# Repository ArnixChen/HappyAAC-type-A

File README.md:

# HappyAAC-type-A
## An open-source main-board to make AAC device makers Happy ;)

## HappyAAC type A
#### 尺寸 8cm x 5cm 角落圓孔直徑 2.86mm
#### 它是一塊針對AAC溝通需求設計的開放電路板,使用者只要把必要的元件焊上電路板,就可以開始動手實作各種功能,免去手工連接大量線路的困難。

1. 使用 Sparkfun Pro Micro控制板, 支援鍵盤或滑鼠模擬功能
2. 內建 BB-4056 鋰電池充電模組線路,有插座可接鋰池及充電
3. 內建 DFPlayer Mini MP3 模組線路,內含一組音訊Line Out 用的插座,可接擴音喇叭,另有一組最大3W迷喇叭接插座
4. 一組音量旋鈕插座
5. 支援最多24個按鈕或特殊開關接點(沒有與其他功能衝突時)
6. 兩組獨立I2C裝置接點
7. 紅外線接收接座, 可以接遙控訊號
8. 紅外線發射接座,可以遙控其他的裝置
9. 留有16組GPIO +VCC+GND 接點,滿足特殊用途的需求
10. 它使用KiCad (open source)電路軟體設計, 並提供原始檔, 可以自己修改設計。

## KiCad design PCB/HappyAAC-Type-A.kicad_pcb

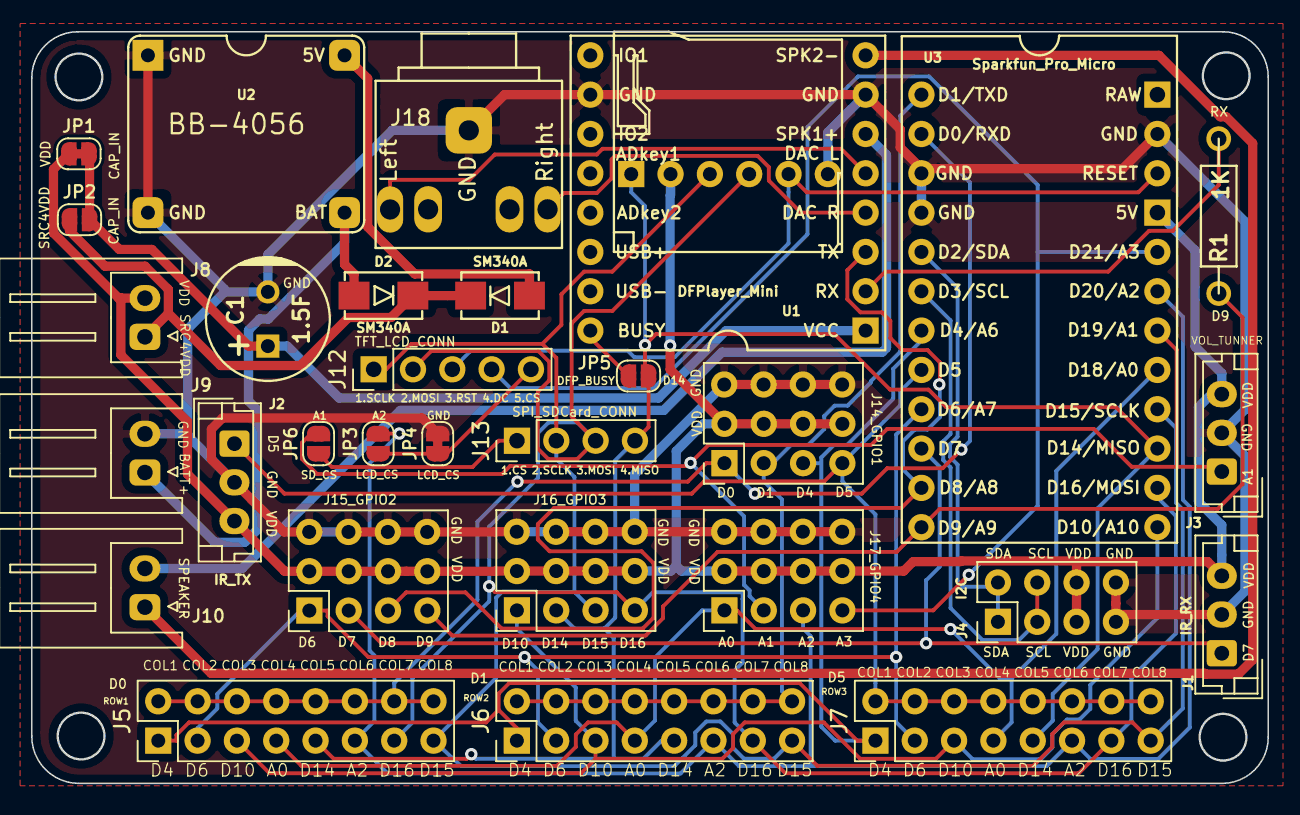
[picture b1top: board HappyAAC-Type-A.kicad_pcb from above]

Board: 2 copper layers, 79.8 x 48.5 mm, 31 parts (0 on the bottom side), 33 nets.

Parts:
C1: 1.5F; CAP_pol_DIP_D8mm
D1, D2: SM340A; SMA_DO214AC_M_SM340A
J1: IR_RX; JST_EH_B3B-EH-A_1x03_P2.50mm_Vertical
J2: IR_TX; JST_EH_B3B-EH-A_1x03_P2.50mm_Vertical
J3: VOL_TUNNER; JST_EH_B3B-EH-A_1x03_P2.50mm_Vertical
J4: I2C; PinHeader_2x04_P2.54mm_Vertical_PadHole0.9mm
J5: ROW1; PinHeader_2x08_P2.54mm_Vertical
J6: ROW2; PinHeader_2x08_P2.54mm_Vertical
J7: ROW3; PinHeader_2x08_P2.54mm_Vertical
J8: PWR_SW; PEC-2503-2H.JST_XH_S2B-XH-A_1x02_P2.50mm_Horizontal
J9: Batt; PEC-2503-2H.JST_XH_S2B-XH-A_1x02_P2.50mm_Horizontal
J10: SPEAKER; PEC-2503-2H.JST_XH_S2B-XH-A_1x02_P2.50mm_Horizontal
J11: ICSP; ICSP_PinHeader_1x06_P2.54mm_Horizontal
J12: TFT_LCD; PinHeader_1x05_P2.54mm_Vertical
J13: SDCard_Conn; PinHeader_1x04_P2.54mm_Vertical
J14_GPIO1, J15_GPIO2, J16_GPIO3, J17_GPIO4: Conn_03x04_Odd_Even_VSG; PinHeader_3x04_P2.54mm_Vertical_PadHole0.9mm
J18: AudioJack; Jack_3.5mm_Arnix_5pin_AudioJack4_Ground_Horizontal
JP1, JP4: SolderJumper_2_Bridged; SolderJumper-2_P1.3mm_Bridged_RoundedPad1.0x1.5mm
JP2, JP3, JP5, JP6: SolderJumper_2_Open; SolderJumper-2_P1.3mm_Open_RoundedPad1.0x1.5mm
R1: 1K; RES_DIP_0.25W_10mm
U1: DFPlayer_Mini; DFPlayer_Mini_BigPad
U2: BB-4056
U3: Sparkfun_Pro_Micro; Sparkfun_Pro_Micro_BigPad

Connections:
+5V: D1.2, U2.4
+BATT: D2.2, J9.1, U2.3
/A0: J5.7, J6.7, J7.7, J17_GPIO4.1, U3.17
/A1: J3.1, J17_GPIO4.2, JP6.2, U3.18
/A2: J5.11, J6.11, J7.11, J17_GPIO4.3, JP3.2, U3.19
/A3: J12.4, J17_GPIO4.4, U3.20
/CAP_IN: C1.1, JP1.2, JP2.2, U1.1
/COL1: J5.1, J6.1, J7.1, J14_GPIO1.3, U3.7
/COL2: J5.3, J6.3, J7.3, J15_GPIO2.1, U3.9
/COL3: J5.5, J6.5, J7.5, J16_GPIO3.1, U3.13
/COL5: J5.9, J6.9, J7.9, J11.1, J13.4, J16_GPIO3.2, JP5.2, U3.15
/COL7: J5.13, J6.13, J7.13, J11.4, J12.2, J13.3, J16_GPIO3.4, U3.14
/COL8: J5.15, J6.15, J7.15, J11.3, J12.1, J13.2, J16_GPIO3.3, U3.16
/D0: J5.2, J5.4, J5.6, J5.8, J5.10, J5.12, J5.14, J5.16, J14_GPIO1.1, U3.2
/D1: J6.2, J6.4, J6.6, J6.8, J6.10, J6.12, J6.14, J6.16, J14_GPIO1.2, U3.1
/D2: J4.1, J4.2, U3.5
/D3: J4.3, J4.4, U3.6
/D5: J2.1, J7.2, J7.4, J7.6, J7.8, J7.10, J7.12, J7.14, J7.16, J14_GPIO1.4, U3.8
/D7: J1.1, J15_GPIO2.2, U3.10
/D8: J15_GPIO2.3, U1.3, U3.11
/D9: J15_GPIO2.4, R1.1, U3.12
/DFP_BUSY: JP5.1, U1.16
/LCD_CS: J12.5, JP3.1, JP4.1
/LCD_RST: J11.5, J12.3, U3.22
/SPK1: J10.2, U1.6
/SPK2: J10.1, U1.8
/SRC_FOR_VDD: D1.1, D2.1, J8.1, JP2.1
GND: C1.2, J1.2, J2.2, J3.2, J4.7, J4.8, J9.2, J11.6, J14_GPIO1.GND, J15_GPIO2.GND, J16_GPIO3.GND, J17_GPIO4.GND, J18.G, JP4.2, U1.7, U1.10, U2.1, U2.2, U3.3, U3.4, U3.23
unnamed: J13.1, JP6.1
unnamed: J18.S, U1.4
unnamed: J18.T, U1.5
unnamed: R1.2, U1.2
VDD: J1.3, J2.3, J3.3, J4.5, J4.6, J8.2, J11.2, J14_GPIO1.VCC, J15_GPIO2.VCC, J16_GPIO3.VCC, J17_GPIO4.VCC, JP1.1, U3.21

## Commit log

2021-06-02 Add some rules to .gitignore
2021-06-02 A good photo say what it is
2021-06-03 Add a picture for parts and functions description
2021-06-03 Add more description
2021-06-03 Move csv files to folder kicad_plugins
2021-06-03 move pictures in root folder into folder pictures/Board
2021-06-03 Add pictures for showing HappyAAC-type-A main parts assembled
2021-06-03 Add application example of phoneBox
2021-06-03 Move documents to Documents folder
2021-06-03 Move pictures into Pictures folder
2021-06-03 Move PCB related files into PCB folder
2021-06-03 Update URL path to fit with former folder rearrangement
2021-06-03 Fix a wrong word mistake
2021-06-03 Replace filename 'IO使用表' with 'IO Table'
2021-06-03 Replace filename '說明' with 'Manual'
2021-06-03 use CC0 1.0 Universal licence
2021-06-04 update user's manual for traditional chinese -- add material list
2021-06-04 Small update
2021-06-04 Add list of materials for HappyAAC type A.
2021-06-04 Shrink HappyAAC-Type-A.Manual.tw.pdf file size
2021-06-05 Update .gitignore to keep .~ prefixed files from being tracked by git
2021-06-05 Update user's manual -- Add Soldering-Guide for significant parts.
2021-06-06 Update HappyAAC-type-A.3D-Front-Side.png (remove 3D through hole parts)
2021-06-06 Update HappyAAC-Type-A.3D-Back-Side.png (remove 3D through hole parts)
2021-06-06 1. Lower the picture resolution to make HappyAAC-Type-A.Manual.odg file small 2. Update Soldering guide section to part II
2021-06-06 Add ignore rule for *.net file
2021-06-06 Update J8 PWR_SW ,J9 BATT_SW ,J10 SPEAKER footprint association to JST_XH_S2B-XH-A_1x02_P2.50mm_Horizontal Update PCB routing
2021-06-06 Update gerber files and 3D pictures and pdf file of schematics
2021-06-06 Update gerber file package to 2021.0607-1
2021-06-06 Update HappyAAC-Type-A.kicad_pcb.Mod.csv to keep new JST-HX-Connector and Header position
2021-06-07 Update Manual -- add Soldering guide for JST-HX Sockets
2021-06-09 Update user's manual - Soldering Guide finished
2021-06-09 Update BOM list
2021-06-09 Update bill of material list
2021-06-09 Add disclaimer and risc of Li-ion battery messages to user's manual
2021-06-10 Correct DO<->ROW1 D1<->ROW2 mapping notes and some messages on schematics
2021-06-10 Correct DO<->ROW1 D1<->ROW2 mapping in IO Table
2021-06-10 Rearrange messages on P.4 to clearify the module's port direction Add some messages on P.7 to emphasize the IR emitter's JST.XH part placement on picture of P.2 is wrong.
2021-06-12 Add pictures of electric-recorder to Application_Example folder
2021-06-12 Add a button side picture of electric-recorder
2021-06-12 Update README.md to emphsize it's ability of open-source
2021-06-17 Remove demo video, maybe it would be better to put videos on somewhere else.
2021-06-17 Add sample code and SD card example for reference.
2021-06-17 I decide not to publish these files because of license issue.
2021-06-22 1. Fix wrong PCB text for R1 (D15-->D9) on F.SilkS and B.SilkS 2. Update PCB version text to 2021.0611-1
2021-07-14 Redo gerber files generating for revision 2d (because the GerberFiles folder has files for both rev 2c and 2d)
2021-08-01 1. Fix footprint of J9 - battery connector, to keep connector's pin defination as text labels printed on the board. 2. Fix footprint of ICSP connector, let it's SilkS shape shows on the back side. 3.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
